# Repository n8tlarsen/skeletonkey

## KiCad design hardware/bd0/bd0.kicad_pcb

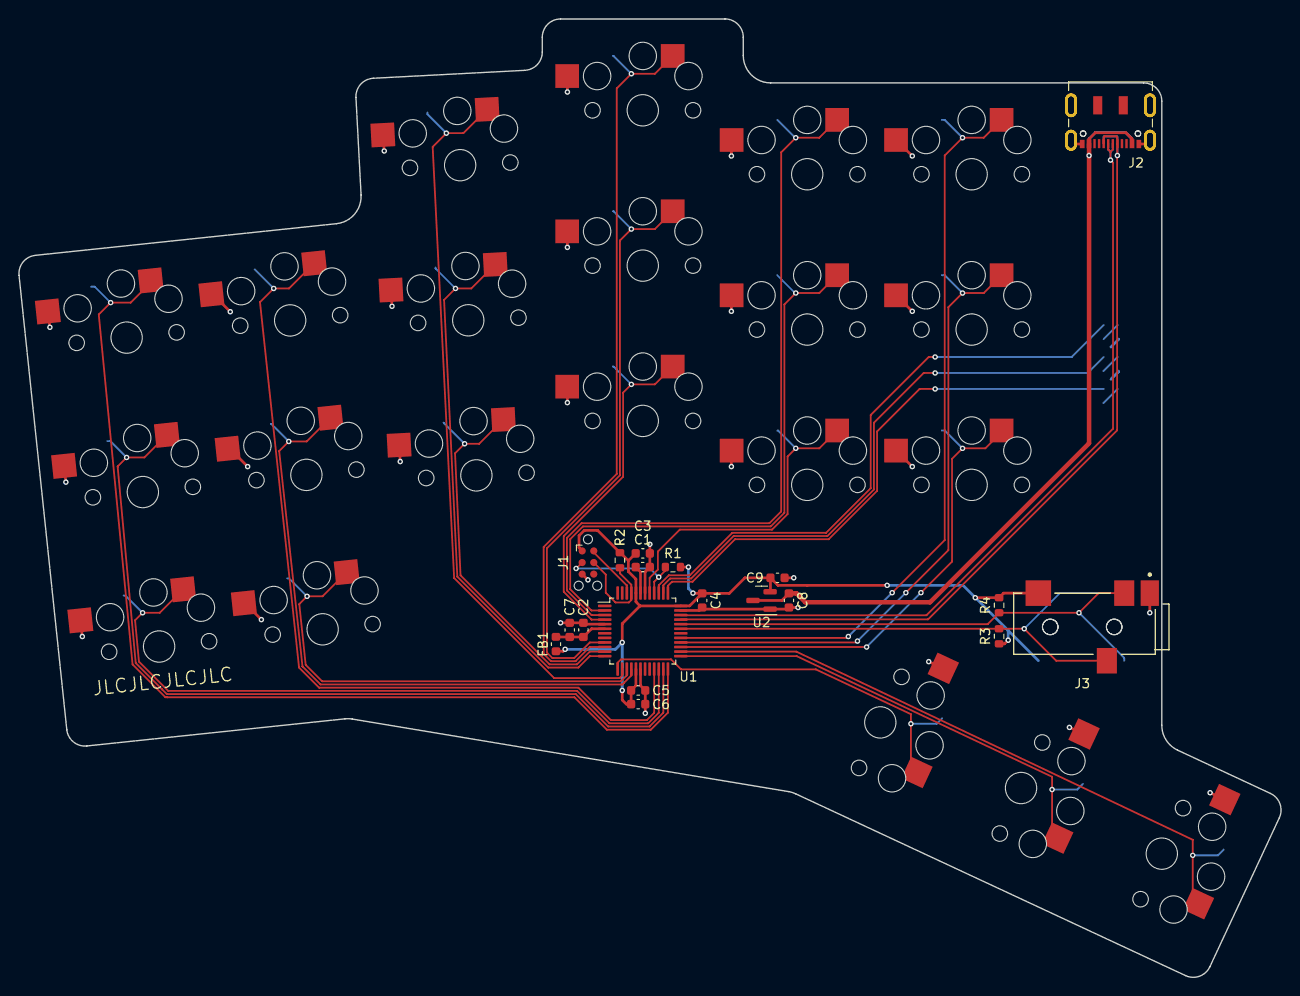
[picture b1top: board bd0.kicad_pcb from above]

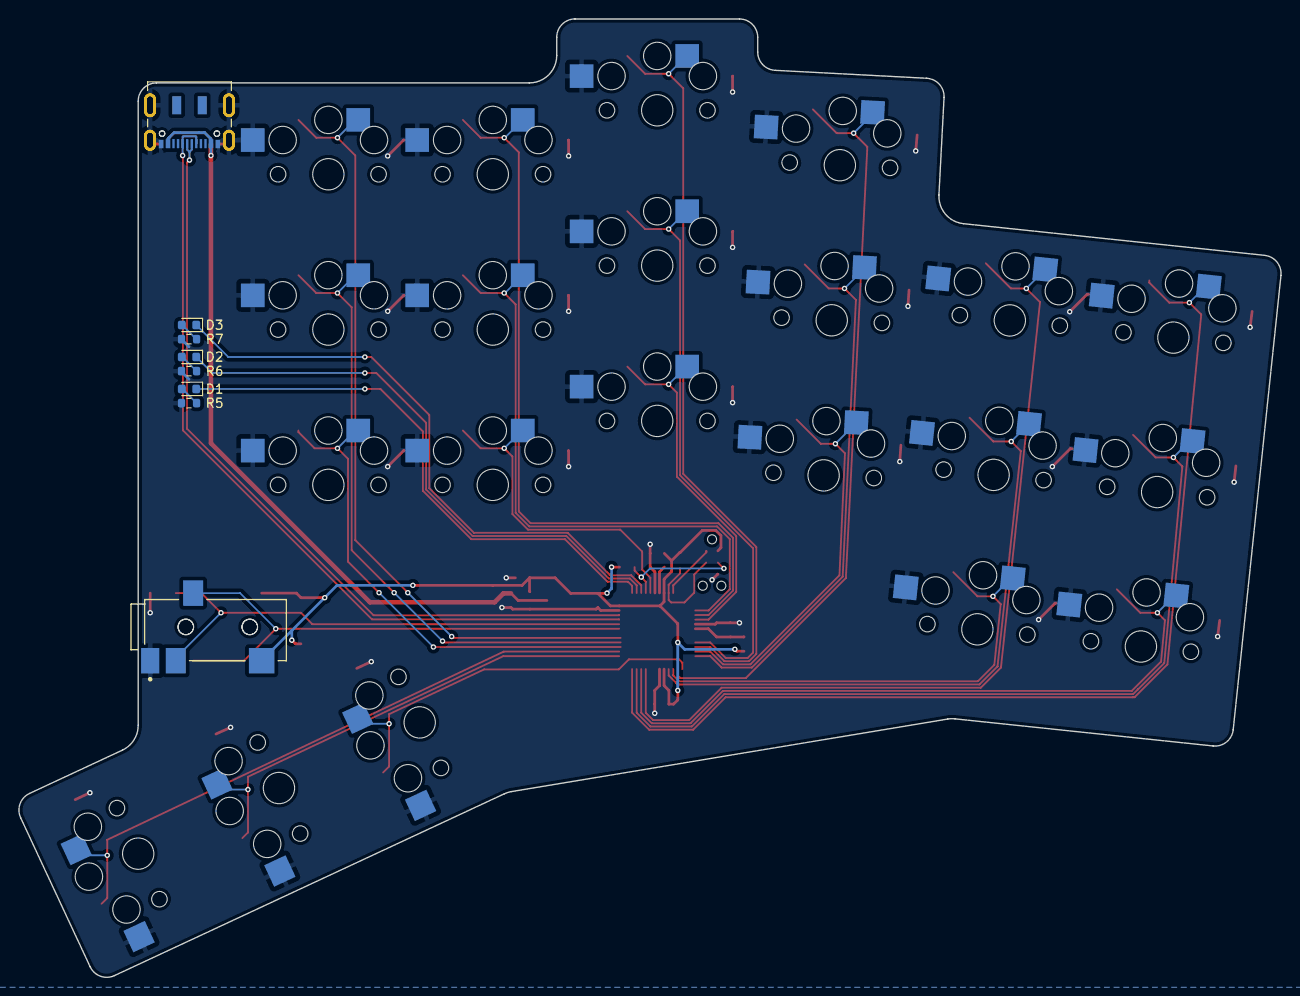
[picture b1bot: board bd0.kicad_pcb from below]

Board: 2 copper layers, 138.2 x 104.9 mm, 48 parts (8 on the bottom side), 39 nets.

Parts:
C1, C8, C9: 1uF; C_0603_1608Metric
C2, C3, C4, C5: 0.1uF; C_0603_1608Metric
C6, C7: 10uF; C_0603_1608Metric
D1, D2, D3: LED; D_0603_1608Metric
FB1: FerriteBead; L_0603_1608Metric
J1: Conn_02x03_Odd_Even; Tag-Connect_TC2030-IDC-NL_2x03_P1.27mm_Vertical
J2, J20: USB_C_Receptacle_USB2.0; USB_C_Receptacle_JAE_DX07S016JA1R1500
J3, J30: SJ-43514; CUI-SJ-43514-SMT-0
R1, R3, R4: 10k; R_0603_1608Metric
R2: 1k; R_0603_1608Metric
R5, R6, R7: 470; R_0603_1608Metric
S1, S2, S3, S4, S5, S6, S7, S8, S9, S10, S11, S12, S13, S14, S15, S16, S17, S18, S19, S20, S21: PG1350
U1: ATSAMD21G15B-A; TQFP-48_7x7mm_P0.5mm
U2: AP2127N-3.3; SOT-23

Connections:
+1V2: C1.1, U1.43 (VDDCORE)
+3V3: C3.1, C4.1, C5.1, C6.1, C9.1, FB1.1, J1.1, J3.2 (Tip), J30.2 (Tip), R1.1, R2.1, R3.1, R4.1, U1.17 (VDDIO), U1.36 (VDDIO), U1.44 (VDDIN), U2.2 (VO)
+5V: C8.1, J2.A4 (VBUS), J2.A9 (VBUS), J2.B4 (VBUS), J2.B9 (VBUS), J20.A4 (VBUS), J20.A9 (VBUS), J20.B4 (VBUS), J20.B9 (VBUS), U2.3 (VI)
/3V3A: C2.1, C7.1, FB1.2, U1.6 (VDDANA)
/LED0: D1.1 (K), U1.37 (PB22)
/LED1: D2.1 (K), U1.38 (PB23)
/LED2: D3.1 (K), U1.39 (PA27)
/RESETn: J1.3, R1.2, U1.40 (~RESET)
/SCL: J3.4 (Ring2), J30.4 (Ring2), R4.2, U1.32 (PA23)
/SDA: J3.3 (Ring1), J30.3 (Ring1), R3.2, U1.31 (PA22)
/SWCLK: J1.4, R2.2, U1.45 (PA30)
/SWDIO: J1.2, U1.46 (PA31)
/USB_DN: J2.A7 (D-), J2.B7 (D-), J20.A7 (D-), J20.B7 (D-), U1.33 (PA24)
/USB_DP: J2.A6 (D+), J2.B6 (D+), J20.A6 (D+), J20.B6 (D+), U1.34 (PA25)
/far_thumb: S21.1, U1.26 (PA17)
/home_thumb: S20.1, U1.25 (PA16)
/index_bottom: S13.1, U1.41 (PA28)
/index_home: S14.1, U1.2 (PA01)
/index_top: S15.1, U1.3 (PA02)
/inner_bottom: S16.1, U1.27 (PA18)
/inner_home: S17.1, U1.28 (PA19)
/inner_top: S18.1, U1.29 (PA20)
/middle_bottom: S10.1, U1.4 (PA03)
/middle_home: S11.1, U1.9 (PA04)
/middle_top: S12.1, U1.10 (PA05)
/near_thumb: S19.1, U1.13 (PA08)
/outer_bottom: S1.1, U1.22 (PA13)
/outer_home: S2.1, U1.23 (PA14)
/outer_top: S3.1, U1.24 (PA15)
/pinky_bottom: S4.1, U1.15 (PA10)
/pinky_home: S5.1, U1.16 (PA11)
/pinky_top: S6.1, U1.21 (PA12)
/ring_bottom: S7.1, U1.11 (PA06)
/ring_home: S8.1, U1.12 (PA07)
/ring_top: S9.1, U1.14 (PA09)
GND: C1.2, C2.2, C3.2, C4.2, C5.2, C6.2, C7.2, C8.2, C9.2, J1.5, J2.A1 (GND), J2.A12 (GND), J2.B1 (GND), J2.B12 (GND), J2.S1 (SHIELD), J3.1 (Sleeve), J20.A1 (GND), J20.A12 (GND), J20.B1 (GND), J20.B12 (GND), J20.S1 (SHIELD), J30.1 (Sleeve), R5.2, R6.2, R7.2, S1.2, S2.2, S3.2, S4.2, S5.2, S6.2, S7.2, S8.2, S9.2, S10.2, S11.2, S12.2, S13.2, S14.2, S15.2, S16.2, S17.2, S18.2, S19.2, S20.2, S21.2, U1.5 (GNDANA), U1.18 (GND), U1.35 (GND), U1.42 (GND), U2.1 (GND)
unnamed: D1.2 (A), R5.1
unnamed: D2.2 (A), R6.1
unnamed: D3.2 (A), R7.1

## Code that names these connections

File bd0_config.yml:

points:
  key:
    padding: cy
    footprints:
      keychoc:
        type: choc
        nets:
          from: =keynet
          to: GND
        params:
          hotswap: true
          reverse: true
          keycaps: true
  zones:
    matrix:
      anchor:
      rows:
        bottom:
          bind: [1,2,1,2]
        home:
          bind: [1,2,1,2]
        top:
          bind: [1,2,1,2]
      columns:
        outer:
          spread: cx
          rotate: 6
          row_overrides:
            bottom:
              keynet: /outer_bottom
            home:
              keynet: /outer_home
            top:
              keynet: /outer_top
        pinky:
          spread: cx
          row_overrides:
            bottom:
              keynet: /pinky_bottom
            home:
              keynet: /pinky_home
            top:
              keynet: /pinky_top
        ring:
          spread: cx+0.5
          rotate: -3
          stagger: 15
          row_overrides:
            bottom:
              keynet: /ring_bottom
            home:
              keynet: /ring_home
            top:
              keynet: /ring_top
        middle:
          spread: cx+0.5
          rotate: -3
          stagger: 5
          row_overrides:
            bottom:
              keynet: /middle_bottom
            home:
              keynet: /middle_home
            top:
              keynet: /middle_top
        index:
          spread: cx
          stagger: -7
          row_overrides:
            bottom:
              keynet: /index_bottom
            home:
              keynet: /index_home
            top:
              keynet: /index_top
        inner:
          spread: cx
          row_overrides:
            bottom:
              keynet: /inner_bottom
            home:
              keynet: /inner_home
            top:
              keynet: /inner_top
    thumbfan:
      anchor:
        ref: matrix_inner_bottom
        shift: [-10, -26]
        rotate: -25
      rows:
        thumb:
          bind: [1,2,1,2]
      columns:
        near:
          key:
            rotate: -90
          row_overrides:
            thumb:
              keynet: /near_thumb
        home:
          spread: cy
          key:
            rotate: -90
          row_overrides:
            thumb:
              keynet: /home_thumb
        far:
          spread: cy
          key:
            rotate: -90
          row_overrides:
            thumb:
              keynet: /far_thumb
outlines:
  exports:
    raw:
      - type: keys
        side: left
        size: [cx, cx]
      - operation: add
        type: polygon
        points: 
          - ref: matrix_pinky_bottom
            shift: [0,-cy/2-1]
          - ref: thumbfan_far_thumb
            # shift: [0   , cy/2]
          - ref: matrix_inner_top
            shift: [20.81446479999999, 1.5+cy/2]
          - ref: matrix_index_top
            shift: [0, 1.5+cy/2]
          # - ref: matrix_inner_bottom
          #   shift: [cx/2,cy/2+1]
          - ref: matrix_index_bottom
          - ref: matrix_pinky_home
    cutout:
      - type: outline
        name: raw
        fillet: 3
      - operation: add
        type: outline
        name: raw
        fillet: 2
    keycap_outlines:
      - type: keys
        side: left
        size: [cx-0.5, cy-0.5]
        bound: false

pcbs:
  bd0:
    outlines:
      bd:
        outline: cutout

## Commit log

2022-02-02 Add ergogen config
2022-02-02 Add TRRS connector library
2022-02-02 Add first board
2022-02-06 Change layout to hotswap switch connectors
2022-02-13 Finished BD0 schematic and routing
2022-02-19 Edit local USB-C footprint to meet DRC
2022-02-19 Add signature and output generation
2022-02-19 Ignore zip files
2022-02-26 Specify black solder mask
2022-03-12 Add CMake project and vscode settings
